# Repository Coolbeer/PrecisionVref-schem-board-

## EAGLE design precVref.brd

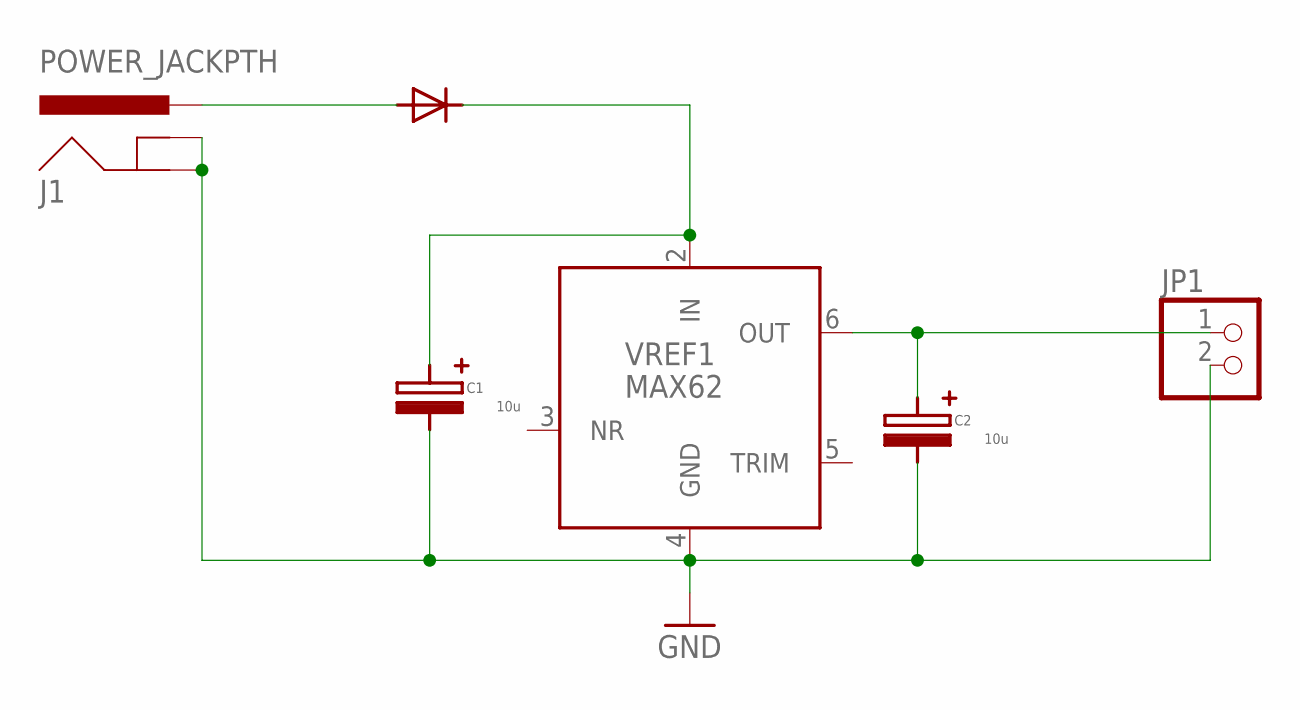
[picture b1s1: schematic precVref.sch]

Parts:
C1, C2: 10u; CPOL1,5/5
D1: D7/2X5; DO-41
J1: POWER_JACKPTH; POWER_JACK_PTH
JP1: PINHD-1X2; 1X02
VREF1: MAX62; SOIC-8

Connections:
GND: C1.P$1 (NEG), C2.P$1 (NEG), J1.GND, J1.GNDBREAK, JP1.2, VREF1.4 (GND)
unnamed: C1.P$2 (POS), D1.CATHODE, VREF1.2 (IN)
unnamed: C2.P$2 (POS), JP1.1, VREF1.6 (OUT)
unnamed: D1.ANODE, J1.PWR

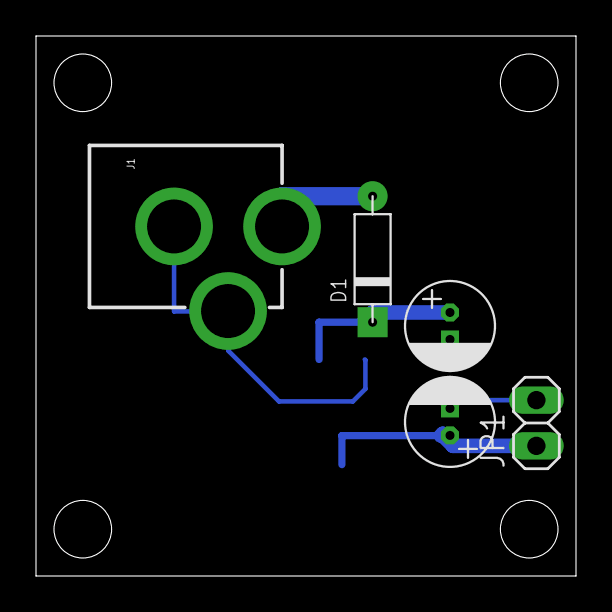
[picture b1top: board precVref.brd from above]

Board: 2 copper layers, 30.0 x 30.0 mm, 6 parts (1 on the bottom side), 4 nets.

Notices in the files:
parts and their libraries:
SparkFun: Licensing: CC v3.0 Share-Alike You are welcome to use this library for commercial purposes.
